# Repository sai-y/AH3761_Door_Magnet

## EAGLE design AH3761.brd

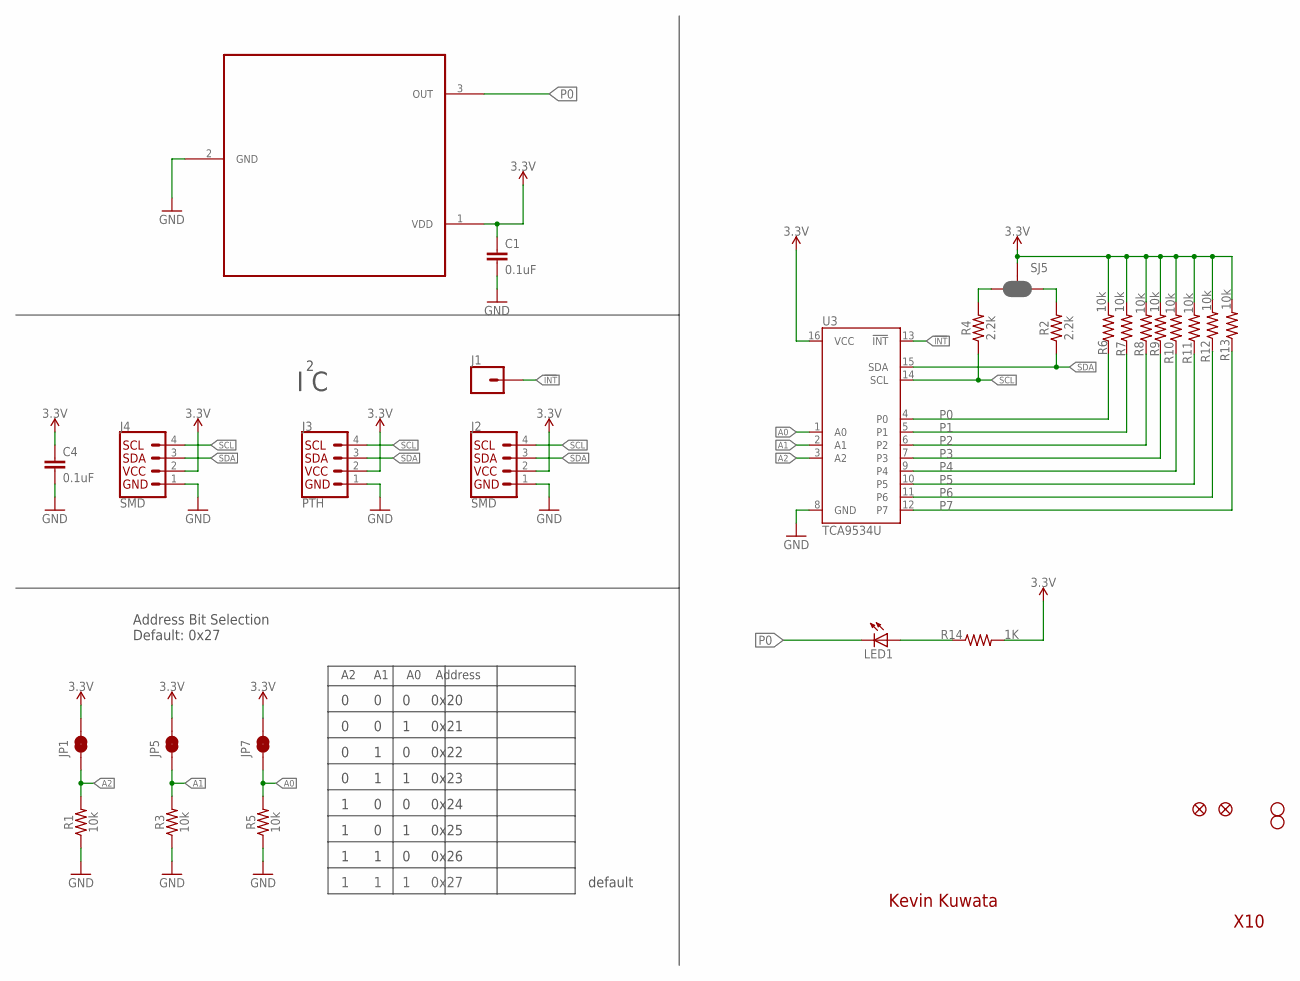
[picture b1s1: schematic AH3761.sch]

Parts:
C1, C4: 0.1uF; 0603
J1: CONN_01PTH_NO_SILK_YES_STOP; 1X01_NO_SILK
J2, J4: SMD; 1X04_1MM_RA
J3: PTH; 1X04_NO_SILK
JP1, JP5, JP7: JUMPER-SMT_2_NC_TRACE_NO-SILK; SMT-JUMPER_2_NC_TRACE_NO-SILK
JP2, JP6: FIDUCIALUFIDUCIAL; MICRO-FIDUCIAL
JP3, JP4: STAND-OFF
LED1: LEDCHIPLED_0603; CHIPLED_0603
R1, R3, R5, R6, R7, R8, R9, R10, R11, R12, R13: 10k; 0603
R2, R4: 2.2k; 0603
R14: 1K; R0603
SJ5: SMT-JUMPER-_3-2-NC-PASTE_TALL; SMT-JUMPER_3-2-NC-PASTE_SILK_TALLER_A
U3: TCA9534U; 16SOIC
U$1: AH3761; SC-59

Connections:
3.3V: C1.1, C4.1, J2.2 (VCC), J3.2 (VCC), J4.2 (VCC), JP1.2, JP5.2, JP7.2, R6.2, R7.2, R8.2, R9.2, R10.2, R11.2, R12.2, R13.2, R14.2, SJ5.2, U3.16 (VCC), U$1.1 (VDD)
!INT: J1.1, U3.13 (!INT)
A0: JP7.1, R5.2, U3.1 (A0)
A1: JP5.1, R3.2, U3.2 (A1)
A2: JP1.1, R1.2, U3.3 (A2)
GND: C1.2, C4.2, J2.1 (GND), J3.1 (GND), J4.1 (GND), R1.1, R3.1, R5.1, U3.8 (GND), U$1.2 (GND)
unnamed: LED1.A, R14.1
P0: LED1.C, R6.1, U3.4 (P0), U$1.3 (OUT)
P1: R7.1, U3.5 (P1)
P2: R8.1, U3.6 (P2)
P3: R9.1, U3.7 (P3)
P4: R10.1, U3.9 (P4)
P5: R11.1, U3.10 (P5)
P6: R12.1, U3.11 (P6)
P7: R13.1, U3.12 (P7)
SCL: J2.4 (SCL), J3.4 (SCL), J4.4 (SCL), R4.1, U3.14 (SCL)
SCL_PU1: R2.2, SJ5.1
SDA: J2.3 (SDA), J3.3 (SDA), J4.3 (SDA), R2.1, U3.15 (SDA)
SDA_PU1: R4.2, SJ5.3

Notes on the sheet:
Kevin Kuwata
X10
I C
Address Bit Selection Default: 0x27
A2 A1 A0 Address
0 0 0 0x20
0 0 1 0x21
0 1 0 0x22
0 1 1 0x23
1 0 0 0x24
1 0 1 0x25
1 1 0 0x26
1 1 1 0x27
default

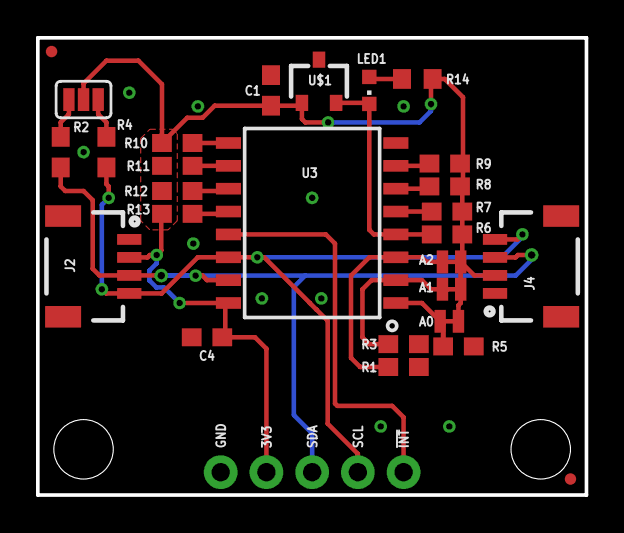
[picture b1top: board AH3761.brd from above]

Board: 2 copper layers, 30.5 x 25.4 mm, 31 parts (0 on the bottom side), 19 nets.

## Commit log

2018-06-07 Checking in image

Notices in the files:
parts and their libraries:
SparkFun-Resistors: Licensing: Creative Commons ShareAlike 4.0 International - https://creativecommons.org/licenses/by-sa/4.0
